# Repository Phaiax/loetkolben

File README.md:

##### Why?

The soldering iron station I used was much older than me and had a few drawbacks, including a random heat-to-infinity function if you don't pay attention. So I decided to renew it, but using the old housing and transformers.

##### PCB:

For more Information refer to the pcb, its full of comments.

+ pcb/alte_schaltung_*.*     - the legacy reverse engeneered pcb. (Including switch, trimmer and plugs which are not directly on the pcb)
+ pcb/neue_schaltung.*	     - my new pcb, double sided, excluding switches, the trimmer, the plugs.
+ pcb/out/		     - this is outdated and need to be regenerated! (the 7905 has different pinouts)

##### Features:

+ galvanic seperated
+ Auto timeout (currently 2 min)
+ Enough power (<30s to 300°C)
+ Temperature Display
+ Switch heat on @ zero passing of sine wave.
+ On and off via software (turn trim resistor to left/right dead stop)
+ Display in house temperature

##### Missing: 

+ a nice controller (kalman or at least something which can filter the white noise of the measurements). I really would like to improve this, but currently I'm using 2032 od 2048 bytes of flash. An AtTiny861A would have been better :(

##### Build:

+ If you should ever build this, make shure you understand every part of the hardware and the software. You need to calibrate the timer value and the temperature calculation coefficient and offset.
+ Depending on the used voltages and transformers, you may need to adjust some resistors etc.
+ Pay attention when handeling voltages above 30V, and even more attention with 110 or 230V. Always remove plug before opening the housing and vice versa.
+ I needed to force the position of the holes and the led to match the legacy pcb. You may want to move the holes.
+ Check which type of thermocouple (=thermoeelement) you are using and adjust the amplification if neccessary.

##### Possible improvements:

+ Use Attiny861A with 8000 instead of 2000 kb flash and add more features to the software.
+ Make the led to light up at both the positive and negative half wave.
+ Make some EMV improvements.
+ You probably can omit the negative voltage generation, the currently used opamp is capable of only using a positive one. (I former planed to use another opamp).
+ The polygons that create the ground area can be adjusted, so the triac and the led have more spacing to the surrounding ground area.

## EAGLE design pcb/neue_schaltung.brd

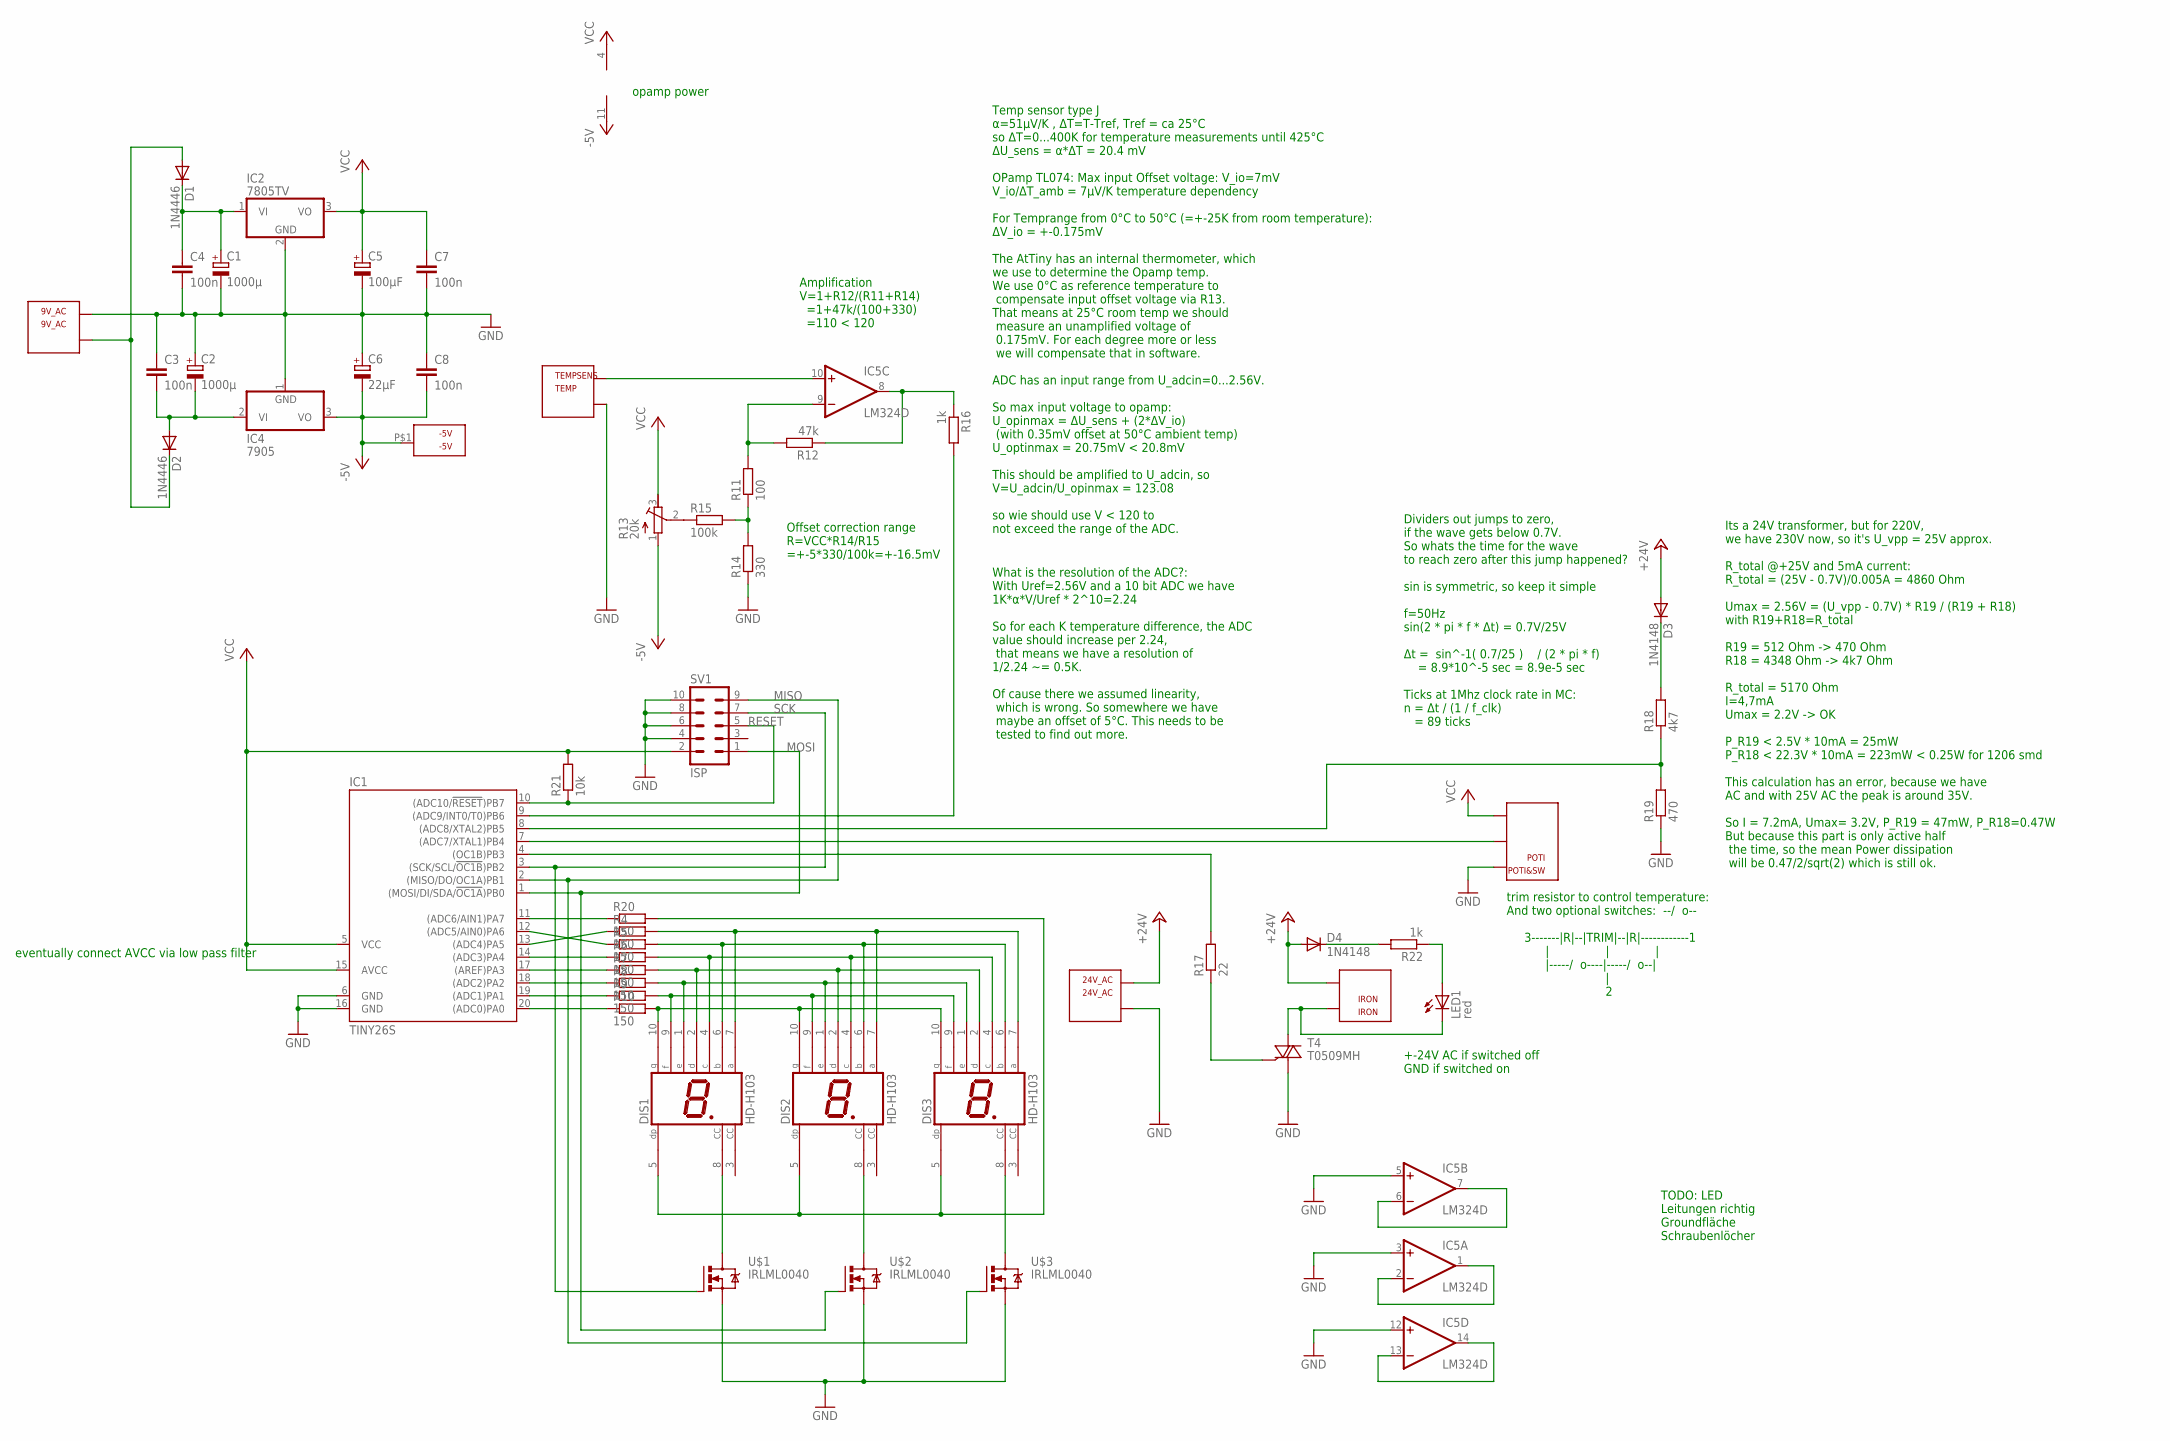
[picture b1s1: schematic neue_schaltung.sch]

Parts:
9V_AC: 9V_AC; WIREPADX2_2H
24V_AC: 24V_AC; WIREPADX2_2H_BIG
-5V: -5V; WIREPAD_2H
C1, C2: 1000µ; E5-10,5
C3, C4, C7, C8: 100n; C0805
C5: 100µF; E2-5
C6: 22µF; E2-5
D1, D2: 1N4446; DO35-10
D3, D4: 1N4148; DO35-10
DIS1, DIS2, DIS3: HD-H103; HDSP-M
IC1: TINY26S; SO20L
IC2: 7805TV; TO220V
IC4: 7905; TO220H
IC5: LM324D; SO14
IRON: IRON; WIREPADX2_2H_BIG
LED1: red; LED5MM
POTI&SW: POTI; WIREPADX3_2H
R4, R5, R6, R7, R8, R9, R10, R20: 150; M1206
R11: 100; M1206
R12: 47k; M1206
R13: 20k; RTRIM64W
R14: 330; M1206
R15: 100k; M1206
R16, R22: 1k; M1206
R17: 22; M1206
R18: 4k7; M1206
R19: 470; M1206
R21: 10k; M1206
SV1: ISP; ML10
T4: T0509MH; TO220AB
TEMPSENS: TEMP; WIREPADX2_2H
U$1, U$2, U$3: IRLML0040; MICRO3

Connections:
+24V: 24V_AC.P$1, D3.A, D4.A, IRON.P$2
-5V: -5V.P$1, C6.-, C8.2, IC4.3 (VO), IC5.11 (V-), R13.1 (E)
GND: 9V_AC.P$1, 24V_AC.P$2, C1.-, C2.+, C3.1, C4.2, C5.-, C6.+, C7.2, C8.1, IC1.6 (GND), IC1.16 (GND), IC2.2 (GND), IC4.1 (GND), IC5.3 (+IN), IC5.5 (+IN), IC5.12 (+IN), POTI&SW.P$1, R14.1, R19.1, SV1.4, SV1.6, SV1.8, SV1.10, T4.1 (A1), TEMPSENS.P$2, U$1.2 (S), U$2.2 (S), U$3.2 (S)
MISO: IC1.2 ((MISO/DO/OC1A)PB1), SV1.9, U$3.1 (G)
MOSI: IC1.1 ((MOSI/DI/SDA/!OC1A!)PB0), SV1.1, U$2.1 (G)
unnamed: DIS1.10 (G), DIS2.10 (G), DIS3.10 (G), R10.2
unnamed: DIS1.9 (F), DIS2.9 (F), DIS3.9 (F), R9.2
unnamed: DIS1.1 (E), DIS2.1 (E), DIS3.1 (E), R8.2
unnamed: DIS1.2 (D), DIS2.2 (D), DIS3.2 (D), R7.2
unnamed: DIS1.4 (C), DIS2.4 (C), DIS3.4 (C), R6.2
unnamed: DIS1.6 (B), DIS2.6 (B), DIS3.6 (B), R5.2
unnamed: DIS1.7 (A), DIS2.7 (A), DIS3.7 (A), R4.2
unnamed: DIS1.5 (DP), DIS2.5 (DP), DIS3.5 (DP), R20.2
unnamed: IC1.12 ((ADC5/AIN0)PA6), R5.1
unnamed: IC1.13 ((ADC4)PA5), R4.1
unnamed: IC1.14 ((ADC3)PA4), R6.1
unnamed: IC1.17 ((AREF)PA3), R7.1
unnamed: IC1.18 ((ADC2)PA2), R8.1
unnamed: IC1.19 ((ADC1)PA1), R9.1
unnamed: IC1.20 ((ADC0)PA0), R10.1
unnamed: DIS1.8 (CC), U$1.3 (D)
unnamed: DIS2.8 (CC), U$2.3 (D)
unnamed: DIS3.8 (CC), U$3.3 (D)
unnamed: IC5.10 (+IN), TEMPSENS.P$1
unnamed: R13.2 (S), R15.1
unnamed: 9V_AC.P$2, D1.A, D2.C
unnamed: C2.-, C3.2, D2.A, IC4.2 (VI)
unnamed: C1.+, C4.1, D1.C, IC2.1 (VI)
unnamed: IC5.9 (-IN), R11.2, R12.2
unnamed: IC1.9 ((ADC9/INT0/T0)PB6), R16.2
unnamed: R11.1, R14.2, R15.2
unnamed: IC5.8 (OUT), R12.1, R16.1
unnamed: IRON.P$1, LED1.K (C), T4.2 (A2)
unnamed: R17.1, T4.3 (G)
unnamed: IC1.4 ((OC1B)PB3), R17.2
unnamed: IC1.7 ((ADC7/XTAL1)PB4), POTI&SW.P$2
unnamed: IC1.8 ((ADC8/XTAL2)PB5), R18.1, R19.2
unnamed: D3.C, R18.2
unnamed: IC1.11 ((ADC6/AIN1)PA7), R20.1
unnamed: D4.C, R22.2
unnamed: IC5.6 (-IN), IC5.7 (OUT)
unnamed: IC5.1 (OUT), IC5.2 (-IN)
unnamed: IC5.13 (-IN), IC5.14 (OUT)
unnamed: LED1.A, R22.1
RESET: IC1.10 ((ADC10/!RESET!)PB7), R21.1, SV1.5
SCK: IC1.3 ((SCK/SCL/!OC1B!)PB2), SV1.7, U$1.1 (G)
VCC: C5.+, C7.1, IC1.5 (VCC), IC1.15 (AVCC), IC2.3 (VO), IC5.4 (V+), POTI&SW.P$3, R13.3 (A), R21.2, SV1.2

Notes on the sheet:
eventually connect AVCC via low pass filter
opamp power
Offset correction range R=VCC*R14/R15 =+-5*330/100k=+-16.5mV
Amplification V=1+R12/(R11+R14) =1+47k/(100+330) =110 < 120
Temp sensor type J α=51µV/K , ΔT=T-Tref, Tref = ca 25°C so ΔT=0...400K for temperature measurements until 425°C ΔU_sens = α*ΔT = 20.4 mV OPamp TL074: Max input Offset voltage: V_io=7mV V_io/ΔT_amb = 7µV/K temperature dependency For Temprange from 0°C to 50°C (=+-25K from room temperature): ΔV_io = 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
What is the resolution of the ADC?: With Uref=2.56V and a 10 bit ADC we have 1K*α*V/Uref * 2^10=2.24 So for each K temperature difference, the ADC value should increase per 2.24, that means we have a resolution of 1/2.24 ~= 0.5K. Of cause there we assumed linearity, which is wrong. So somewhere we 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
+-24V AC if switched off GND if switched on
trim resistor to control temperature: And two optional switches: --/ o-- 3-------|R|--|TRIM|--|R|------------1 | | | |-----/ o----|-----/ o--| | 2
Its a 24V transformer, but for 220V, we have 230V now, so it's U_vpp = 25V approx. R_total @+25V and 5mA current: R_total = (25V - 0.7V)/0.005A = 4860 Ohm Umax = 2.56V = (U_vpp - 0.7V) * R19 / (R19 + R18) with R19+R18=R_total R19 = 512 Ohm -> 470 Ohm R18 = 4348 Ohm -> 4k7 Ohm R_total = 5170 Ohm I=4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
Dividers out jumps to zero, if the wave gets below 0.7V. So whats the time for the wave to reach zero after this jump happened? sin is symmetric, so keep it simple f=50Hz sin(2 * pi * f * Δt) = 0.7V/25V Δt = sin^-1( 0.7/25 ) / (2 * pi * f) = 8.9*10^-5 sec = 8.9e-5 sec Ticks at 1Mhz clock rate in MC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
TODO: LED Leitungen richtig Groundfläche Schraubenlöcher

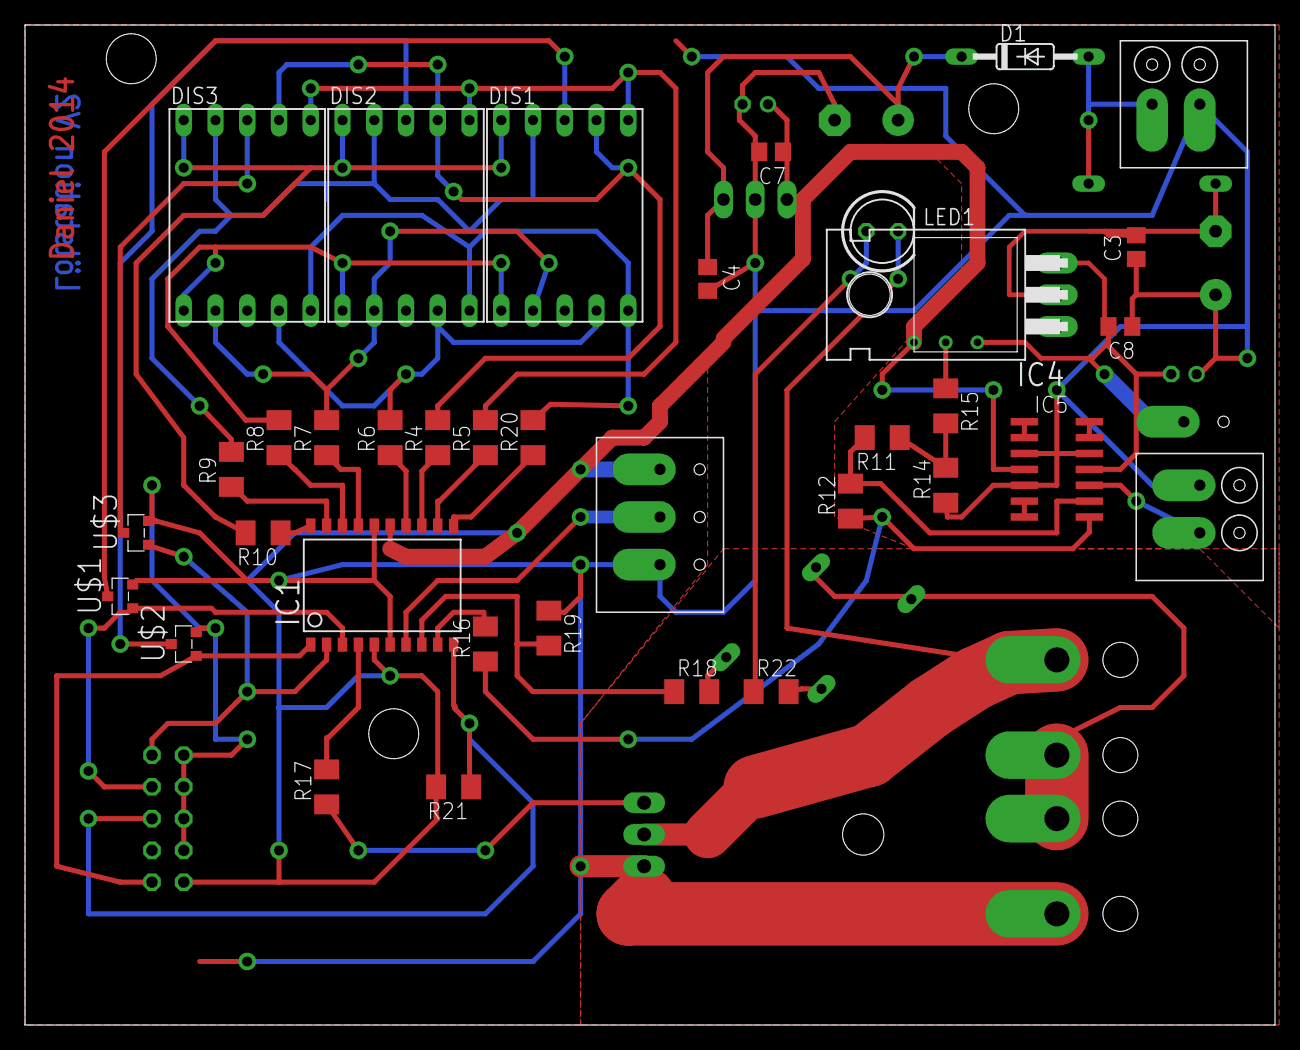
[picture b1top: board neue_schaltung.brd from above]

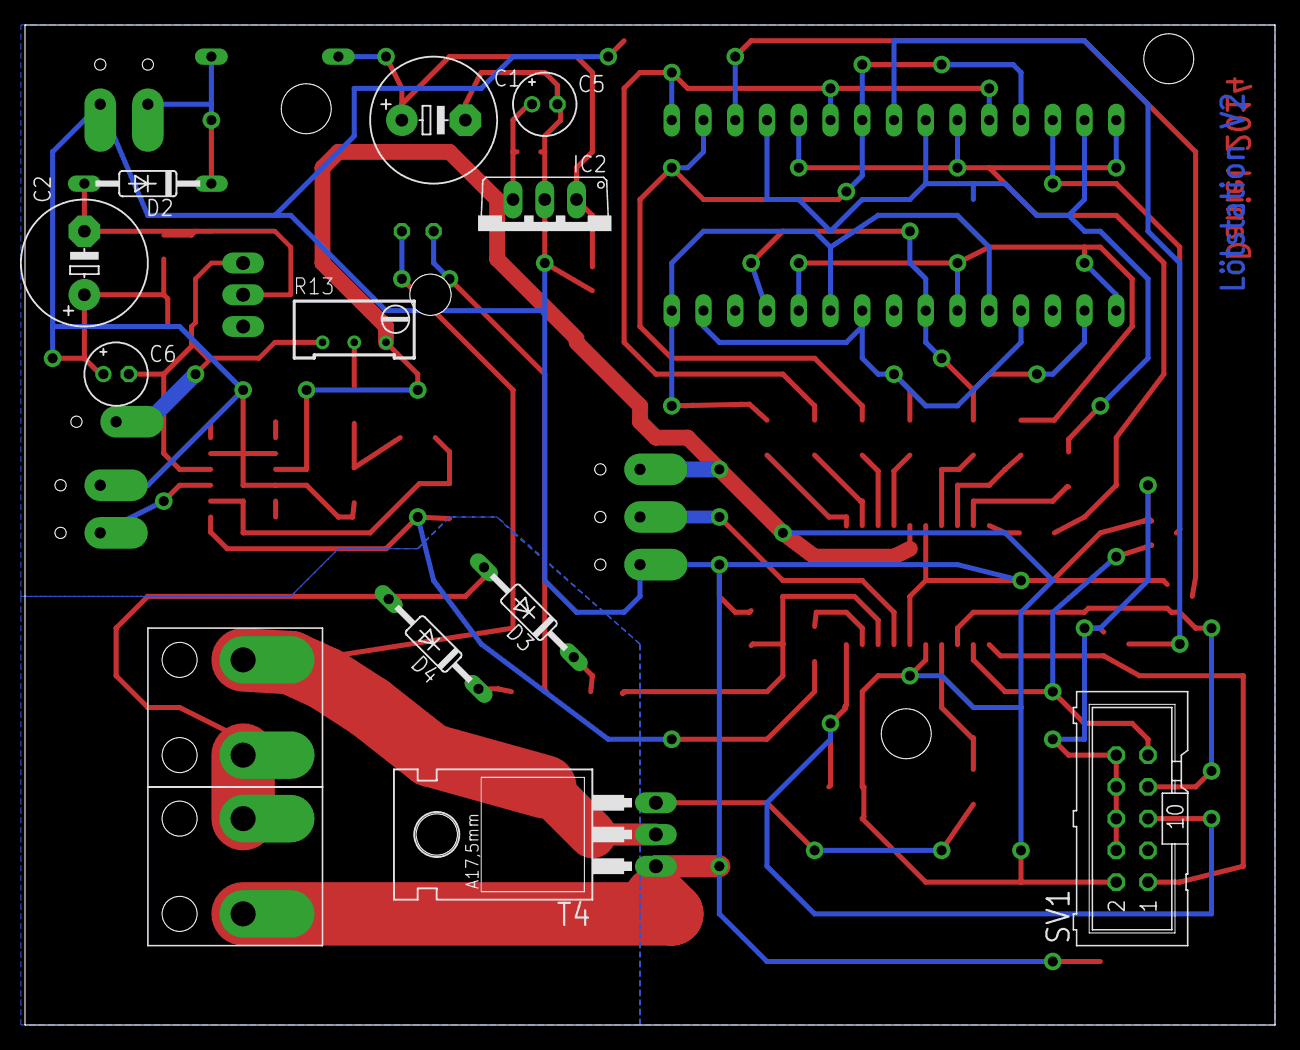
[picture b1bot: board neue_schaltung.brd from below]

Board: 2 copper layers, 100.0 x 80.0 mm, 50 parts (13 on the bottom side), 47 nets.

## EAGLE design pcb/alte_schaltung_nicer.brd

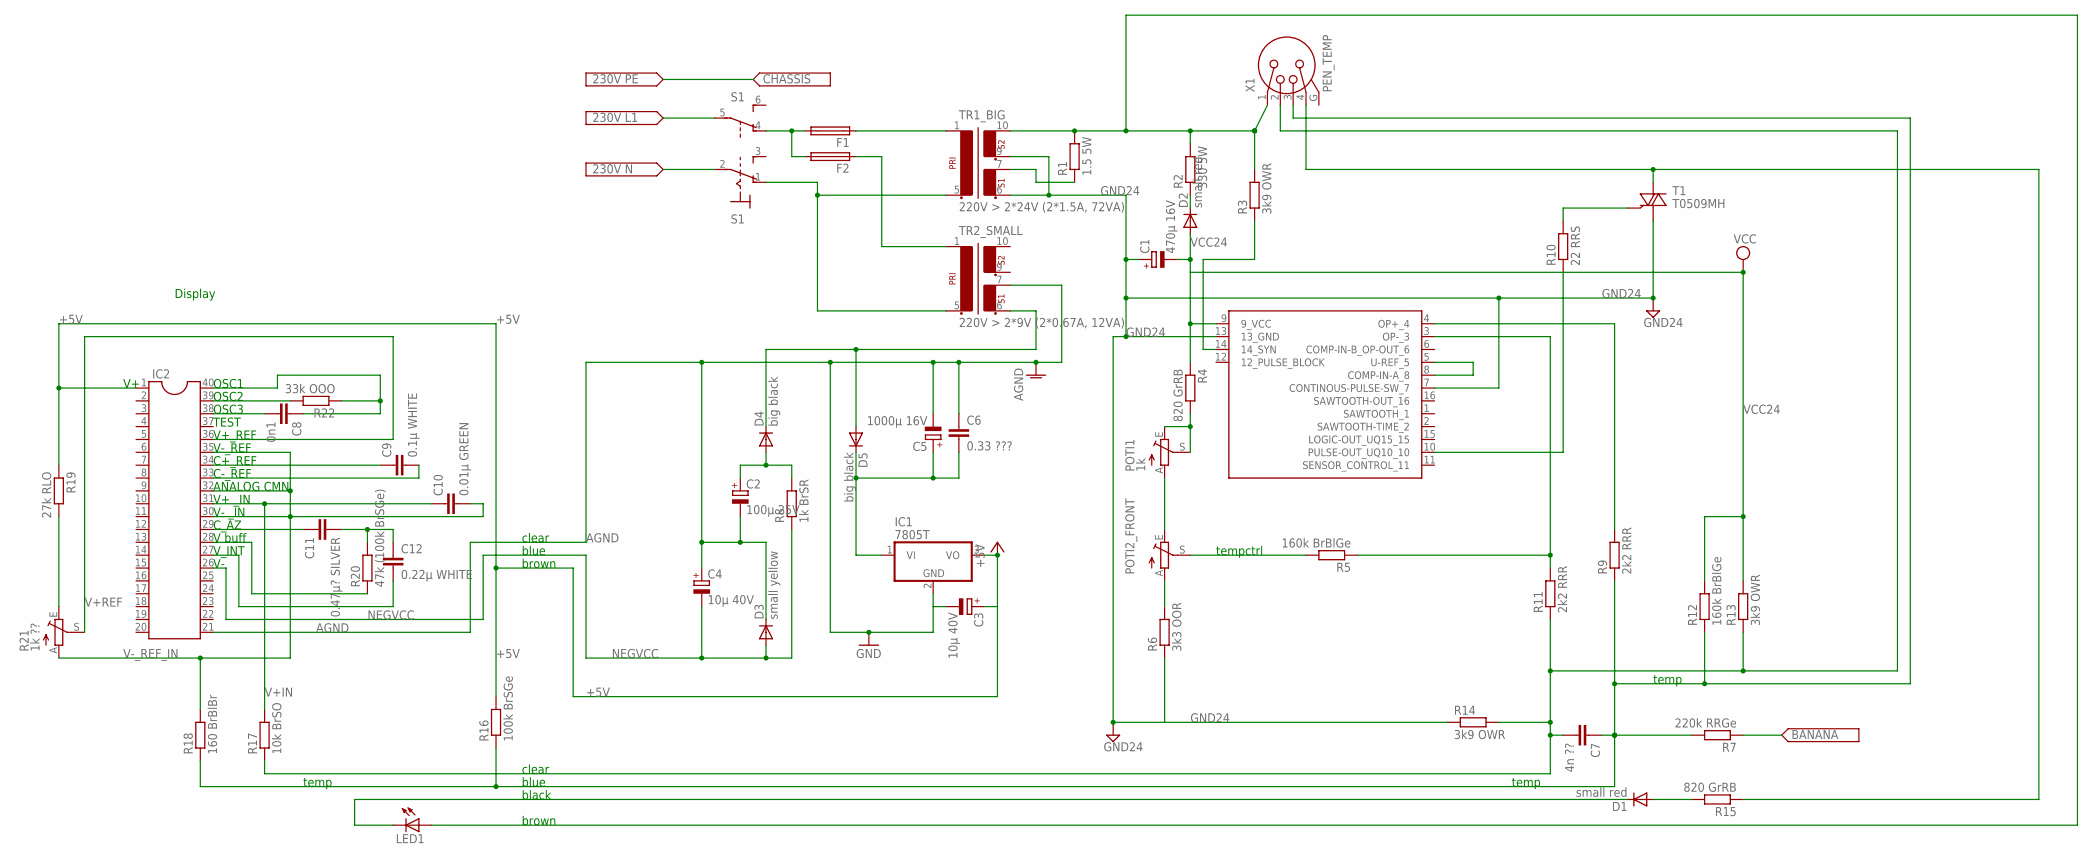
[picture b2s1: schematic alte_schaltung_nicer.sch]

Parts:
C1: 470µ 16V; E5-10,5
C2: 100µ 25V; E5-10,5
C3, C4: 10µ 40V; E5-10,5
C5: 1000µ 16V; E5-10,5
C6: 0.33 ???; C075-042X103
C7: 4n ??; C050-024X044
C8: 0n1; C050-024X044
C9: 0.1µ WHITE; C102-043X133
C10: 0.01µ GREEN; C102-043X133
C11: 0.47µ? SILVER; C102-043X133
C12: 0.22µ WHITE; C102-043X133
D1, D2: small red; DO41-10
D3: small yellow; DO35-10
D4, D5: big black; DO41-10
F1, F2: SH25
IC1: 7805T; TO220H
IC2: DIL40
LED1: LED3MM
POTI1: 1k; LI10
POTI2_FRONT: TRIM_EU-RJ9W; RJ9W
R1: 1.5 5W; 0922/22
R2: 330 5W; 0922/22
R3, R13, R14: 3k9 OWR; 0207/12
R4, R15: 820 GrRB; 0207/12
R5, R12: 160k BrBlGe; 0207/12
R6: 3k3 OOR; 0207/12
R7: 220k RRGe; 0207/12
R8: 1k BrSR; 0207/12
R9, R11: 2k2 RRR; 0207/12
R10: 22 RRS; 0207/12
R16: 100k BrSGe; 0207/12
R17: 10k BrSO; 0207/12
R18: 160 BrBlBr; 0207/12
R19: 27k RLO; 0207/12
R20: 47k (100k BrSGe); 0207/12
R21: 1k ??; SP19L
R22: 33k OOO; 0207/12
S1: 320-938
T1: T0509MH; TO220AB
TR1_BIG: 220V > 2*24V (2*1.5A, 72VA); EI42-2
TR2_SMALL: 220V > 2*9V (2*0.67A, 12VA); EI42-2
U$1: U106BS-DIL16; DIL16
X1: PEN_TEMP; NC4FBV

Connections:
+5V: C3.+, IC1.3 (VO), IC2.1, R16.2, R19.1
AGND: C2.-, C3.-, C4.+, C5.-, C6.1, D3.C, IC1.2 (GND), IC2.21, TR2_SMALL.7 (4)
GND24: C1.+, R6.1, R14.1, T1.1 (A1), TR1_BIG.6 (3), TR1_BIG.9 (5), U$1.7 (CONTINOUS-PULSE-SW_7), U$1.13 (13_GND)
unnamed: F1.2, F2.2, S1.4 (O)
unnamed: F1.1, TR1_BIG.1
unnamed: F2.1, TR2_SMALL.1
unnamed: S1.1 (O), TR1_BIG.5 (2), TR2_SMALL.5 (2)
unnamed: C12.2, IC2.27
unnamed: LED1.A, R1.2, R2.2, R3.2, TR1_BIG.10 (6), X1.1
unnamed: R1.1, TR1_BIG.7 (4)
unnamed: D4.C, D5.A, TR2_SMALL.6 (3)
unnamed: C2.+, D4.A, R8.2
unnamed: C5.+, C6.2, D5.C, IC1.1 (VI)
unnamed: D1.A, R15.2
unnamed: R9.2, U$1.4 (OP+_4)
unnamed: C7.1, R7.2, R9.1, R12.1, R16.1, R18.1, X1.3
unnamed: D1.C, LED1.K (C)
unnamed: POTI2_FRONT.S, R5.2
unnamed: C7.2, R11.1, R13.1, R14.2, R17.1, X1.2
unnamed: POTI2_FRONT.A, R6.2
unnamed: R15.1, T1.2 (A2), X1.4
unnamed: R5.1, R11.2, U$1.3 (OP-_3)
unnamed: D2.C, R2.1
unnamed: R19.2, R21.E
unnamed: POTI1.A, POTI2_FRONT.E
unnamed: POTI1.E, POTI1.S, R4.2
unnamed: R10.2, T1.3 (G)
unnamed: R10.1, U$1.10 (PULSE-OUT_UQ10_10)
unnamed: U$1.5 (U-REF_5), U$1.8 (COMP-IN-A_8)
unnamed: R3.1, U$1.14 (14_SYN)
unnamed: C8.2, IC2.38
unnamed: IC2.39, R22.2
unnamed: C8.1, IC2.40, R22.1
unnamed: IC2.28, R20.1
unnamed: C9.1, IC2.34
unnamed: C9.2, IC2.33
unnamed: C11.1, IC2.29
unnamed: C11.2, C12.1, R20.2
NEGVCC: C4.-, D3.A, IC2.26, R8.1
V+IN: C10.1, IC2.31, R17.2
V+REF: IC2.36, R21.S
V-_REF_IN: C10.2, IC2.30, IC2.32, IC2.35, R18.2, R21.A
VCC24: C1.-, D2.A, R4.1, R12.2, R13.2, U$1.9 (9_VCC)

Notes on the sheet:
Display
brown
black
blue
clear
temp
tempctrl
V buff
C_AZ
V_INT
ANALOG CMN
V- _IN
V+ _IN
C+_REF
C-_REF
V+_REF
V-_REF
OSC1
OSC2
OSC3
TEST

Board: 2 copper layers, 52 parts (0 on the bottom side), 43 nets, no tracks yet.

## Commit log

2014-07-29 solderingiron project init commit: display number on breadboard 7seg
2014-07-29 ADC read and display
2014-08-01 Read of trim, now using 3 seven segment displays, so no more rotation
2014-08-01 timer1 for display multiplex, trim range
2014-08-03 final version 1
2014-08-03 Test linking directory
2014-08-03 adding pcb
2014-08-03 add readme
2014-08-03 modify readme
